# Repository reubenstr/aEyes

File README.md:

# aEyes

aEyes is a robotic art project adding physicality to the ubiquitous surveillance apparatus that we walk beneath daily.

<table>
  <tr>
    <td></td>
  </tr>
</table>

# Overview

The stereo depth camera, with onboard neural processing, detects faces and their relative positions, then feeds the data into a tracking and assignment pipeline that controls the positioning of the eyes. Eye assignments are distributed to the six nearest faces.

# UI

**TODO**

# Pipeline

The pipeline is fairly straight forward and the major parts are: **AI Camera Interface → Face Tracker → Eye Manager → Message Publisher → RPi/LCD/Motors**

<figure>
  
  <figcaption align="center">Pipeline Simplified.</figcaption>
</figure>

# System

The system is split into two subsystems: a **Controller** and **6 Eye units**, all connected over a wired Ethernet network.

# Hardware

**Controller**
- Raspberry Pi 4 (or 5)
- OAK-D W depth camera (USB)
- Mean Well LRS-100-24 AC/DC PSU (24V)
- DC-DC converter 24V → 12V
- DC-DC converter 24V → 5V
- 8-port Ethernet switch

**Eye units (×6)**
- Raspberry Pi 4B
- Waveshare 4" DSI LCD
- Waveshare RS485/CAN Hat
- DC-DC converter 24V → 5V
- 1× MG4010E-i10v3 CAN servo motor (yaw)
- 1× MG4005-v2 CAN servo motor (pitch)

# Installation / Setup / Execution

- [Controller](controller/README.md)
- [Eyes](eye/README.md)
- [Mechanical Notes](docs/MECHANICAL.md)
- [Misc Docs](docs/README.md)

# 3D CAD

aEyes was created in CAD using [OnShape](https://cad.onshape.com). The full assembly may be viewed/exported with this link: [aEyes CAD Assembly](https://cad.onshape.com/documents/3d927fbbde33024eb0f3feca/w/105fa9c43462d4971ca0f096/e/2fabb45a1dca49857035ca55)

<table>
  <tr>
    <td></td>
    <td></td>
  </tr>
</table>

# AI Disclosure

Project concept, aesthetic, engineering design, and original code base were conceived and executed by the author.

Portions of this codebase were reviewed, revised, and written with the assistance of various coding agents.

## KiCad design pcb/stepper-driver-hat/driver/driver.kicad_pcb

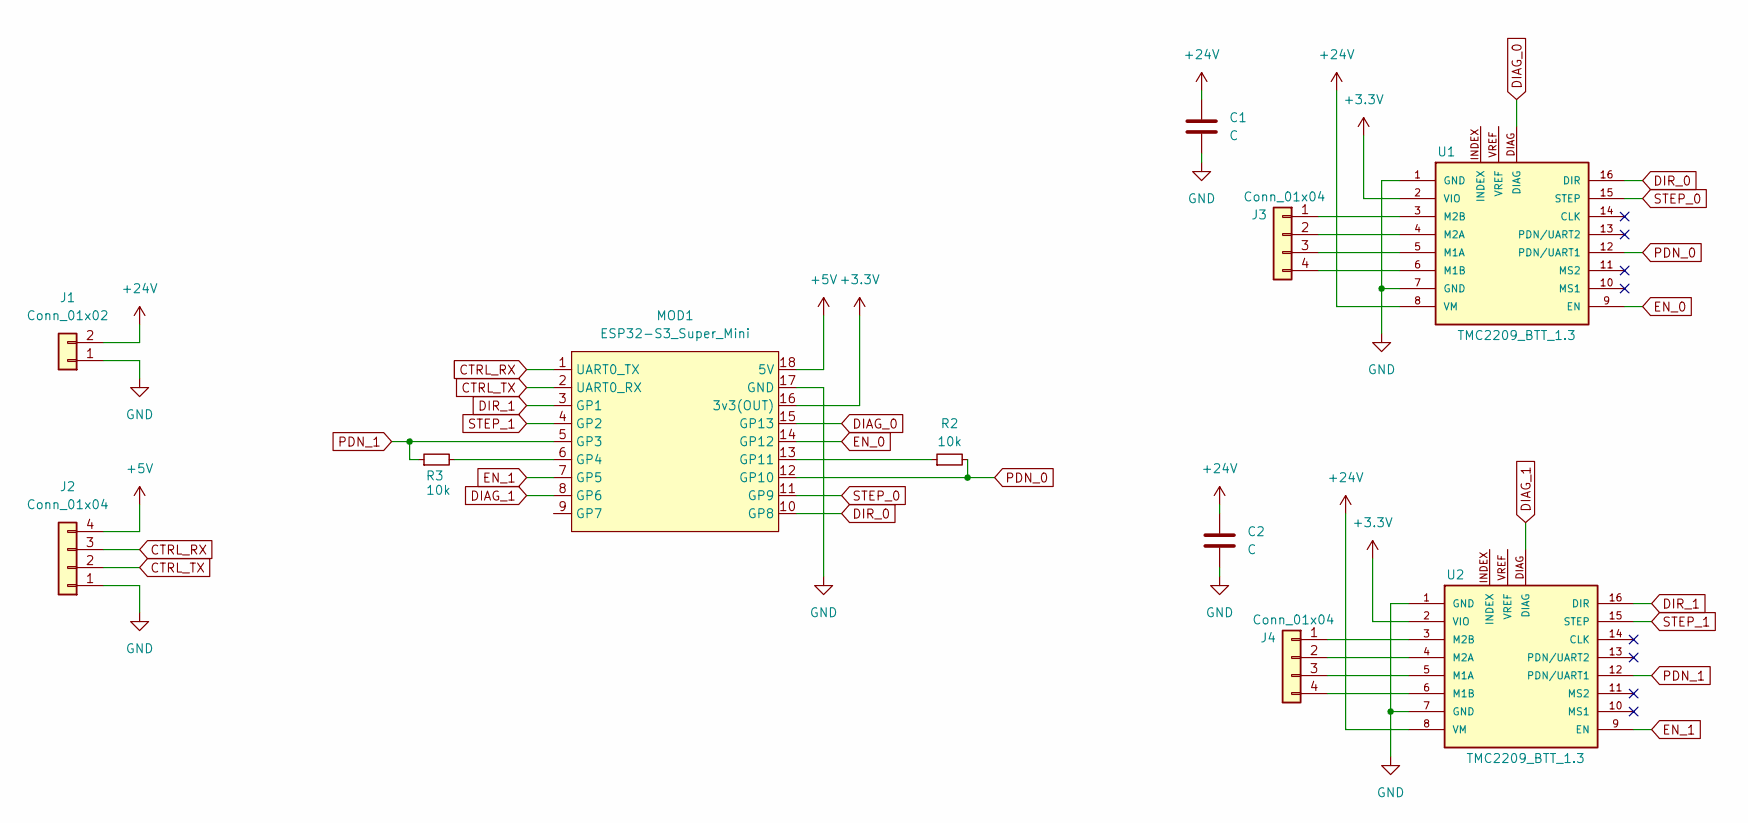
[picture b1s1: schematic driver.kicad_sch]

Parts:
C1, C2: C; CP_Radial_D10.0mm_P5.00mm
J1: Conn_01x02; PinHeader_1x02_P2.54mm_Vertical
J2, J3, J4: Conn_01x04; PinHeader_1x04_P2.54mm_Vertical
MOD1: ESP32-S3_Super_Mini; ESP32-S3 Super Mini
R2, R3: 10k; R_1206_3216Metric
U1, U2: TMC2209_BTT_1.3; MODULE_TMC2208_TMC2209

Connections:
+3.3V: MOD1.16 (3v3(OUT)), U1.2 (VIO), U2.2 (VIO)
+5V: J2.4, MOD1.18 (5V)
+24V: C1.1, C2.1, J1.2, U1.8 (VM), U2.8 (VM)
CTRL_RX: J2.3, MOD1.1 (UART0_TX)
CTRL_TX: J2.2, MOD1.2 (UART0_RX)
DIAG_0: MOD1.15 (GP13), U1.DIAG
DIAG_1: MOD1.8 (GP6), U2.DIAG
DIR_0: MOD1.10 (GP8), U1.16 (DIR)
DIR_1: MOD1.3 (GP1), U2.16 (DIR)
EN_0: MOD1.14 (GP12), U1.9 (EN)
EN_1: MOD1.7 (GP5), U2.9 (EN)
GND: C1.2, C2.2, J1.1, J2.1, MOD1.17 (GND), U1.1 (GND), U1.7 (GND), U2.1 (GND), U2.7 (GND)
unnamed: J3.1, U1.3 (M2B)
unnamed: J3.2, U1.4 (M2A)
unnamed: J3.3, U1.5 (M1A)
unnamed: J3.4, U1.6 (M1B)
unnamed: J4.1, U2.3 (M2B)
unnamed: J4.2, U2.4 (M2A)
unnamed: J4.3, U2.5 (M1A)
unnamed: J4.4, U2.6 (M1B)
unnamed: MOD1.6 (GP4), R3.2
unnamed: MOD1.13 (GP11), R2.1
PDN_0: MOD1.12 (GP10), R2.2, U1.12 (PDN/UART1)
PDN_1: MOD1.5 (GP3), R3.1, U2.12 (PDN/UART1)
STEP_0: MOD1.11 (GP9), U1.15 (STEP)
STEP_1: MOD1.4 (GP2), U2.15 (STEP)

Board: 2 copper layers, 11 parts (0 on the bottom side), 26 nets, no tracks yet.

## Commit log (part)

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2026-01-22 upload preliminary render tets
2026-01-22 testing shader vars
2026-01-22 testing sauron
2026-01-22 sauron working - but going to revert to eye
2026-01-22 back to eye demo
2026-01-22 eye on rpi working
2026-01-23 colors and rotation added
2026-01-23 class structures created
2026-01-23 Add message
2026-01-24 basic updates
2026-01-24 pcb schem update
2026-01-25 motor test
2026-01-27 esp32 comm started
2026-01-27 stepper driver update
2026-01-28 cleanup
2026-01-28 connecting zmq basics
2026-01-28 clean up
2026-01-28 frag cleanup, better blink, cat eye shadow fix
2026-01-29 add motor commands to messages
2026-01-29 firmeware update
2026-01-29 add pixel to firmware, other cleanups
2026-01-29 doc update; install script started
2026-01-29 install.sh update and fixes
2026-01-29 startup fixes, misc
2026-01-29 install.sh update
2026-02-02 can motor test success
2026-02-07 doc update
2026-02-16 update motors
2026-02-16 removed control dataclass from renderer
2026-02-16 update to update pi script
2026-02-17 rm bak file
2026-02-17 add zero script
2026-02-17 remove old firmware, etc.
2026-02-19 rsync script add
2026-02-22 install script update
2026-02-22 add min and max position
2026-02-23 add rotation to install script
2026-02-24 inference crudely workng
2026-02-24 headless depth script first round
2026-02-24 variation tests
2026-02-24 apply claude updates
2026-02-25 conversions started
2026-02-25 building classes, data flowing crudely
2026-02-25 stash
2026-02-26 clean up; pre add gimbal arm transform
2026-02-26 cornea motion fix
2026-02-26 gimbal arm t added and appears to be working
2026-02-26 add display to detector, change to letterbox from crop
2026-03-09 file update
2026-03-10 managers update
2026-03-11 general updates
2026-03-21 update scripts for key copy and shutdown of pis
2026-03-22 update scripts
2026-03-22 readme update
2026-03-22 scripts update
2026-03-22 add motor not zeroed protection
2026-03-23 minor updates
2026-03-28 eye inits and fixes
2026-03-28 update/cleanup eye demo
2026-03-28 add demo to update eyes and visualize data via python gui
2026-03-28 fix motor homing bug
2026-03-28 controller updates to prep for full pipeline
2026-03-28 full pipeline working (jetson)
2026-03-28 motor tweaks
2026-03-28 update sigterm on main.py for eye to prevent shutdown issues
2026-03-29 motor speed ramping applied first pass
2026-03-29 tweaks
2026-03-29 pre-params
2026-03-29 post params
2026-03-29 update demo visual colors
2026-03-29 add static face filter
2026-05-23 image update
2026-05-23 add comments to scripts
2026-05-23 apply rotation to installs scripts
2026-05-23 update motor homing
2026-05-23 script fix
2026-05-24 add motor pos test script
2026-05-24 update motor - cleaning up inverts, etc.
2026-05-24 homing fixes
2026-05-25 fixing zero issue
2026-05-25 motor driver various cleanups
2026-05-25 fix motor homing calculation issues
2026-05-26 controller update started
2026-05-26 started
2026-05-26 oak camera started
2026-05-26 detector tests
2026-05-26 basic xyz working
2026-05-26 update controller install script
2026-05-26 reconnect detections with new camera
2026-05-26 script update
2026-05-26 spat calc device move
2026-05-26 update frame params
2026-06-27 detector.py intellisense errors cleanup
2026-06-27 shutdown button started
2026-06-27 update shutdown scripts
2026-06-27 shutdown update
2026-06-28 color update
2026-06-28 update striation color
